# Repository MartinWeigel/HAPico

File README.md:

# HAPico

This PCB provides control of eight MOSFET outputs. These can be controlled through an [Raspberry Pi Pico 2W](https://www.raspberrypi.com/products/raspberry-pi-pico-2/) microcontroller. It is a two-layer PCB and all parts can be handsoldered in case that costs are a concern.

This board was designed using [KiCad 9.0](https://www.kicad.org).

## Design

## Parts

The board requires the following parts. All of them should be easy to handsolder:

Part                   | Quantity | Description
-----------------------|----------|----------------------------
Raspberry Pi Pico 2W   | 1        | Microcontroller
Phoenix MPT-0,5-2-2.54 | 8        | 2-pin Terminalblock
IRLR024N DPAK MOSFET   | 8        | N-Channel MOSFET (55V 17A)
0805 Resistor 470 Ohm  | 8        | Generic Resistor

## License

<br />
This work is licensed under a <a rel="license" href="http://creativecommons.org/licenses/by/4.0/">Creative Commons Attribution 4.0 International License</a>.

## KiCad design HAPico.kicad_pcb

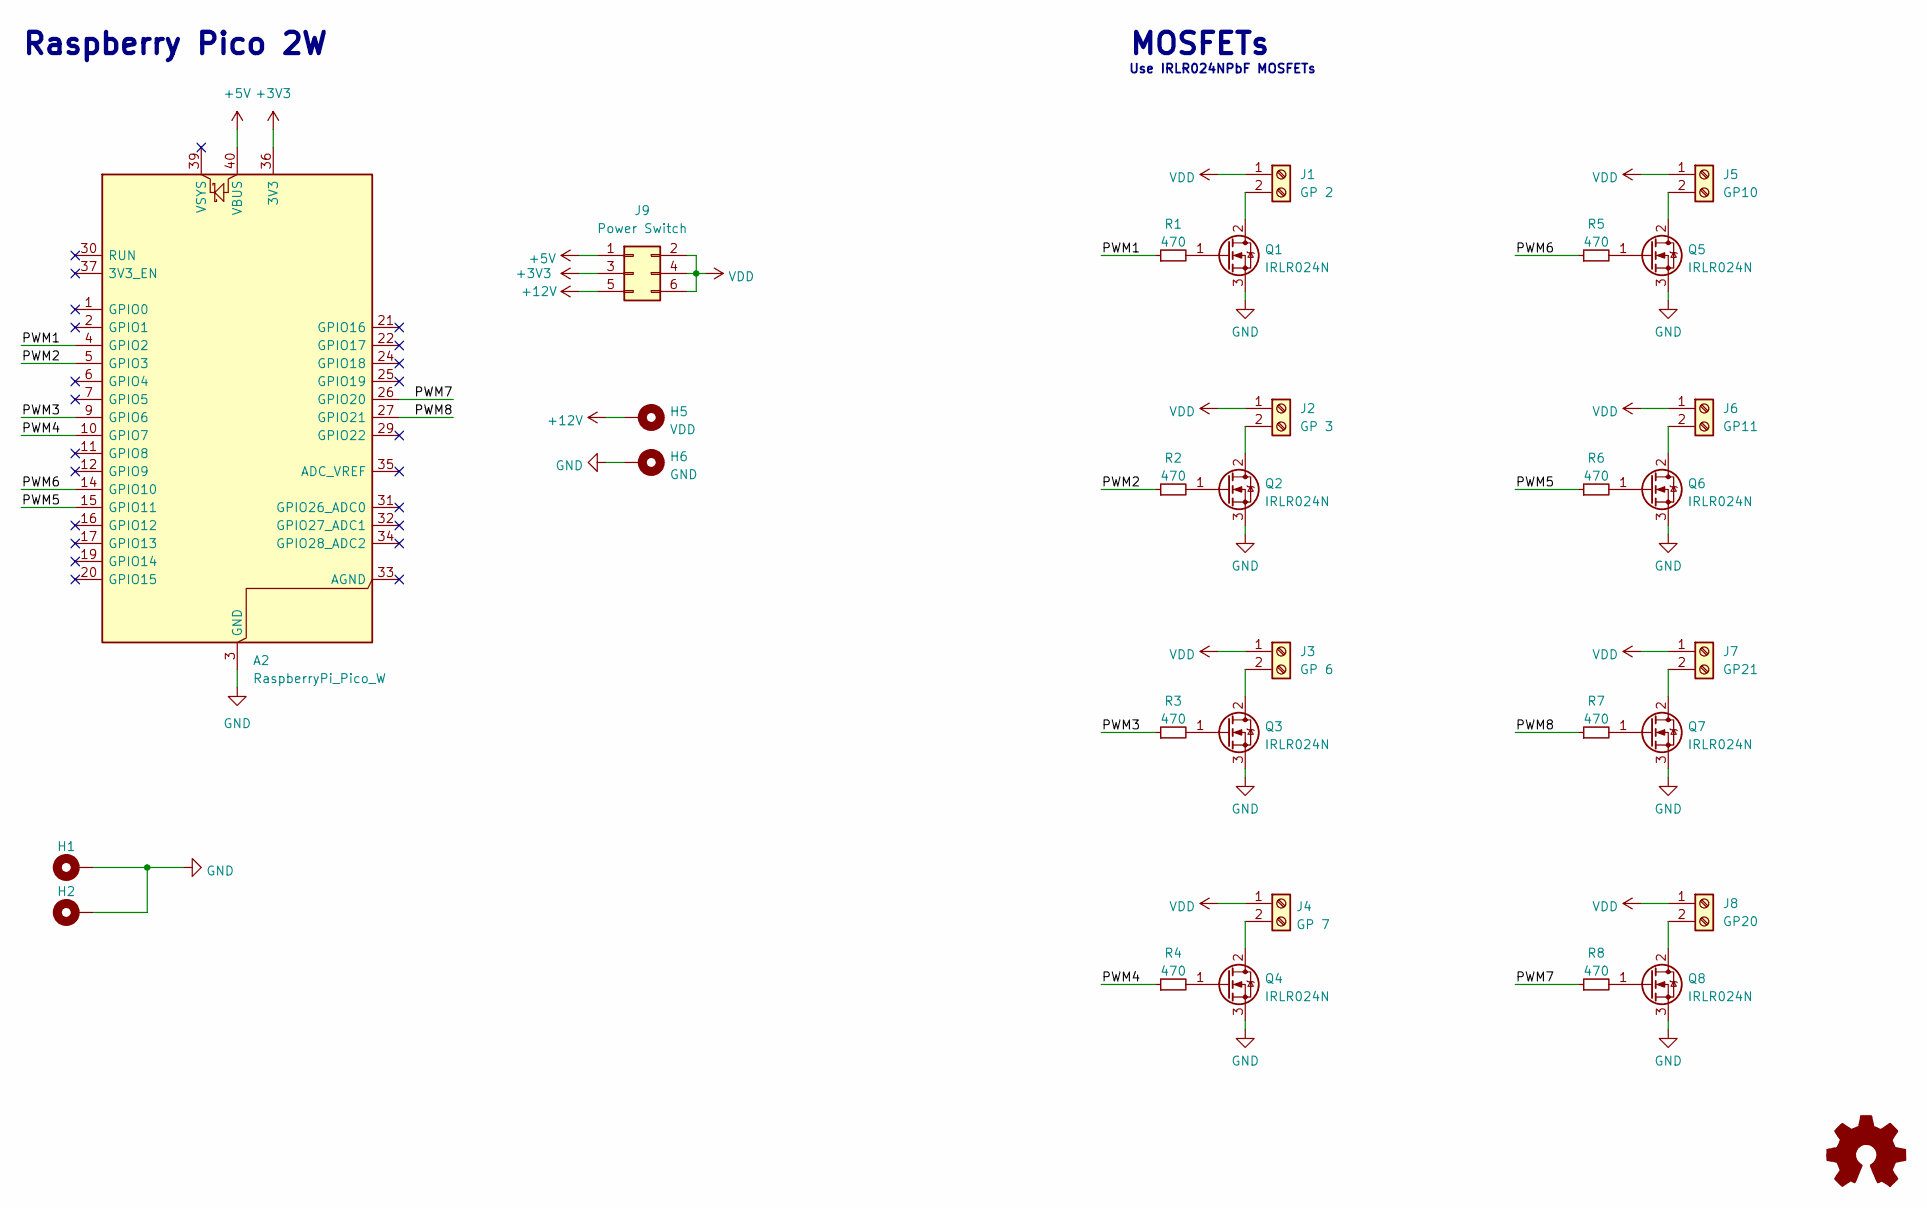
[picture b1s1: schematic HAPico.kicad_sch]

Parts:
A2: RaspberryPi_Pico_W; RaspberryPi_Pico_Common_THT
H1, H2: MountingHole_Pad; MountingHole_3.2mm_M3_DIN965_Pad
H5: VDD; TestPoint_THTPad_4.0x4.0mm_Drill2.0mm
H6: GND; TestPoint_THTPad_4.0x4.0mm_Drill2.0mm
J1: GP 2; TerminalBlock_Phoenix_MPT-0,5-2-2.54_1x02_P2.54mm_Horizontal
J2: GP 3; TerminalBlock_Phoenix_MPT-0,5-2-2.54_1x02_P2.54mm_Horizontal
J3: GP 6; TerminalBlock_Phoenix_MPT-0,5-2-2.54_1x02_P2.54mm_Horizontal
J4: GP 7; TerminalBlock_Phoenix_MPT-0,5-2-2.54_1x02_P2.54mm_Horizontal
J5: GP10; TerminalBlock_Phoenix_MPT-0,5-2-2.54_1x02_P2.54mm_Horizontal
J6: GP11; TerminalBlock_Phoenix_MPT-0,5-2-2.54_1x02_P2.54mm_Horizontal
J7: GP21; TerminalBlock_Phoenix_MPT-0,5-2-2.54_1x02_P2.54mm_Horizontal
J8: GP20; TerminalBlock_Phoenix_MPT-0,5-2-2.54_1x02_P2.54mm_Horizontal
J9: Power Switch; PinHeader_2x03_P2.54mm_Vertical
Q1: IRLR024N; TO-252-2; LCSC PN IRLR024NTRPBF
Q2, Q3, Q4, Q5, Q6, Q7, Q8: IRLR024N; TO-252-2; LCSC IRLR024NTRPBF
R1, R2, R3, R4, R5, R6, R7, R8: 470; R_0805_2012Metric_Pad1.20x1.40mm_HandSolder; LCSC 0805W8F4700T5E

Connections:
+3V3: A2.36 (3V3), J9.3
+5V: A2.40 (VBUS), J9.1
+12V: H5.1, J9.5
/PWM1: A2.4 (GPIO2), R1.1
/PWM2: A2.5 (GPIO3), R2.1
/PWM3: A2.9 (GPIO6), R3.1
/PWM4: A2.10 (GPIO7), R4.1
/PWM5: A2.15 (GPIO11), R6.1
/PWM6: A2.14 (GPIO10), R5.1
/PWM7: A2.26 (GPIO20), R8.1
/PWM8: A2.27 (GPIO21), R7.1
GND: A2.3 (GND), A2.8 (GND), A2.13 (GND), A2.18 (GND), A2.23 (GND), A2.28 (GND), A2.38 (GND), H1.1, H2.1, H6.1, Q1.3 (S), Q2.3 (S), Q3.3 (S), Q4.3 (S), Q5.3 (S), Q6.3 (S), Q7.3 (S), Q8.3 (S)
unnamed: J1.2, Q1.2 (D)
unnamed: J2.2, Q2.2 (D)
unnamed: J3.2, Q3.2 (D)
unnamed: J4.2, Q4.2 (D)
unnamed: J5.2, Q5.2 (D)
unnamed: J6.2, Q6.2 (D)
unnamed: J7.2, Q7.2 (D)
unnamed: J8.2, Q8.2 (D)
unnamed: Q1.1 (G), R1.2
unnamed: Q2.1 (G), R2.2
unnamed: Q3.1 (G), R3.2
unnamed: Q4.1 (G), R4.2
unnamed: Q5.1 (G), R5.2
unnamed: Q6.1 (G), R6.2
unnamed: Q7.1 (G), R7.2
unnamed: Q8.1 (G), R8.2
VDD: J1.1, J2.1, J3.1, J4.1, J5.1, J6.1, J7.1, J8.1, J9.2, J9.4, J9.6

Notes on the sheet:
Raspberry Pico 2W
MOSFETs
Use IRLR024NPbF MOSFETs

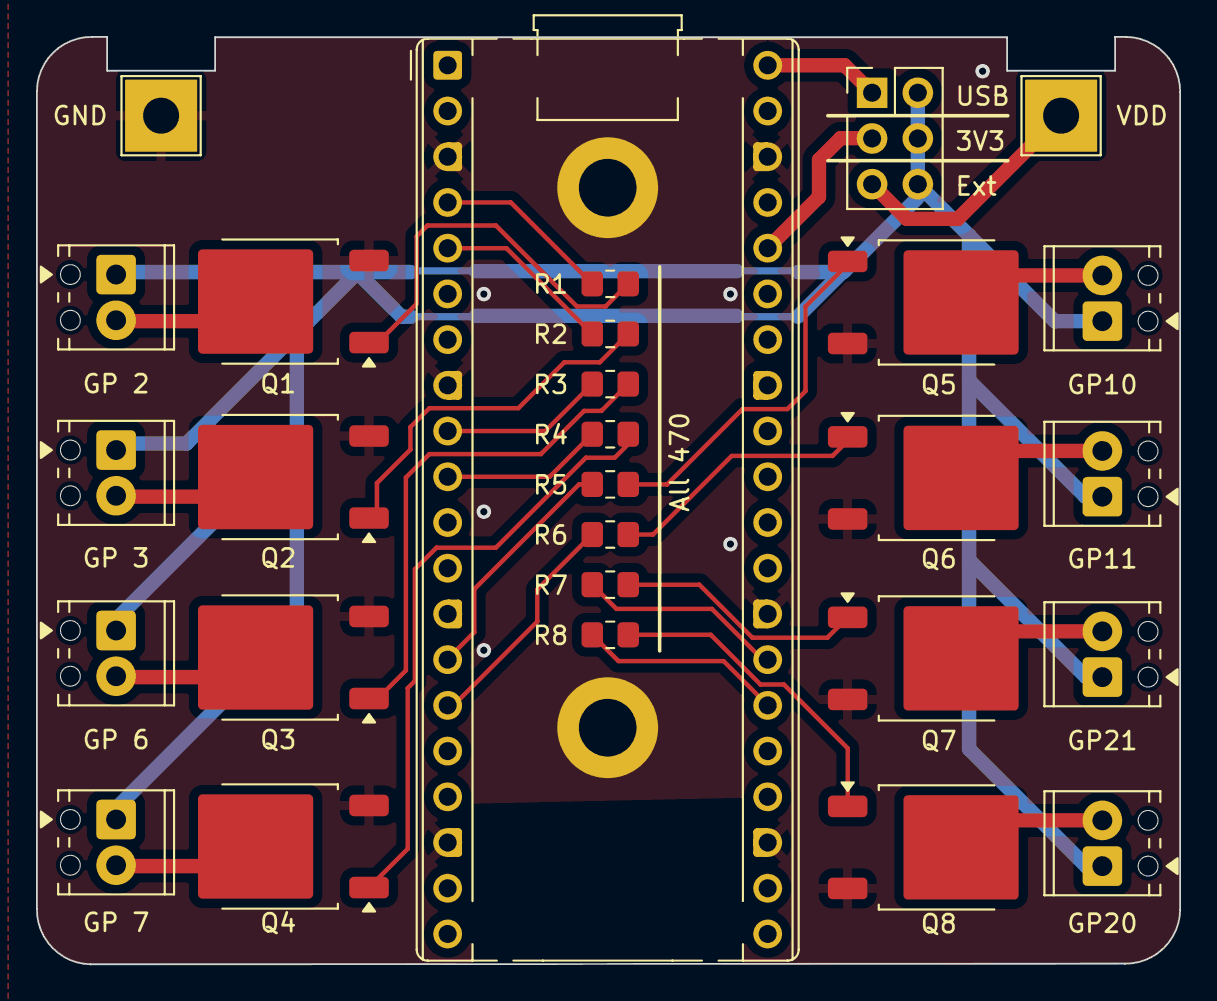
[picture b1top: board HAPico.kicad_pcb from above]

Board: 2 copper layers, 63.5 x 51.5 mm, 30 parts (0 on the bottom side), 29 nets.

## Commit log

2026-01-11 feat: first iteration of HAPico
2026-01-22 fix: GP20 and 21 were swapped

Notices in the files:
HAPico.kicad_pcb:
Author: Martin Weigel License: CC BY 4.0
